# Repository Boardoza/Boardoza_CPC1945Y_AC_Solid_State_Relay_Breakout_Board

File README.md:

# Boardoza CPC1945Y Solid State Relay Breakout Board

The **Boardoza CPC1945Y Breakout Board** is built around the **CPC1945Y AC Solid State Relay (SSR)**, providing safe, silent, and reliable switching of low-power AC loads. Thanks to its optically isolated input and zero-crossing detection structure, it enables noise-free AC switching directly from microcontroller systems.

This board is ideal for applications such as **multiplexers, data acquisition systems, industrial control units, electronic meters (electricity, gas, water), medical devices, security systems, I/O subsystems**, and as a compact and long-lasting **solid-state replacement for mechanical relays**. With no mechanical contacts, it ensures long operational life and vibration-resistant performance.

## [Click here to purchase!](https://www.ozdisan.com/ureticiler/boardoza)

| Front Side | Back Side |
|:---:|:---:|
|  |  |

---

## Key Features

- **Solid State Relay:** Enables reliable AC switching with integrated zero-cross detection for clean transitions.  
- **Optical Isolation:** Provides safe electrical separation between low-voltage control circuits and high-voltage AC loads.  
- **Silent Operation:** No mechanical components, ensuring completely noise-free switching.  
- **Microcontroller Friendly:** Low input current requirement allows direct control from MCU GPIO pins.  
- **Low EMI/RFI:** Zero-cross switching significantly reduces electrical noise during operation.   

---

## Technical Specifications

**Model:** CPC1945Y  
**Manufacturer:** Boardoza  
**Manufacturer IC:** Littelfuse (IXYS Integrated Circuits Division)  
**Functions:** AC Solid State Relay (Optically Isolated)  
**Input Control Type:** DC (LED driven)  
**Typical Input Current:** 5 mA  
**Maximum Recommended Input Current:** 10 mA  
**Output Type:** AC (Zero-Cross)  
**Operating Load Voltage:** 20 – 120 Vac rms  
**Load Current:** Up to 1 A rms    
**Blocking Voltage:** 400 Vp  
**Isolation Voltage:** 3750 Vrms (Input to Output)  
**Operating Temperature:** -40°C to +85°C  
**Board Dimensions:** 20mm x 40mm  

---

## Board Pinout

### ( J1 ) Control Input Connector

| Pin Number | Pin Name | Description |
|:---:|:---:|---|
| 1 | CONTROL | DC Control Input (LED Anode) |
| 2 | GND | Ground (LED Cathode) |

---

### ( J2 ) AC Load Connector

| Pin Number | Pin Name | Description |
|:---:|:---:|---|
| 1 | AC LOAD | AC Output Terminal |
| 2 | AC LOAD | AC Output Terminal |

> The output terminals are non-polarized and internally connected to the SSR output stage.

---

## Board Dimensions

---

## Step Files

[Boardoza CPC1945Y.step](./assets/CPC1945Y%20Step.step)

---

## Datasheet

[CPC1945Y Datasheet.pdf](./assets/CPC1945Y%20Datasheet.pdf)

---

## Version History

- V1.0.0 - Initial Release  

---

## Support

- If you have any questions or need support, please contact **support@boardoza.com**

---

## **License**

### **Hardware Design**

[![CC BY-SA 4.0][cc-by-sa-shield]][cc-by-sa]

All hardware design files are licensed under [Creative Commons Attribution-ShareAlike 4.0 International License][cc-by-sa].

[cc-by-sa]: http://creativecommons.org/licenses/by-sa/4.0/
[cc-by-sa-shield]: https://img.shields.io/badge/License-CC%20BY--SA%204.0-lightgrey.svg

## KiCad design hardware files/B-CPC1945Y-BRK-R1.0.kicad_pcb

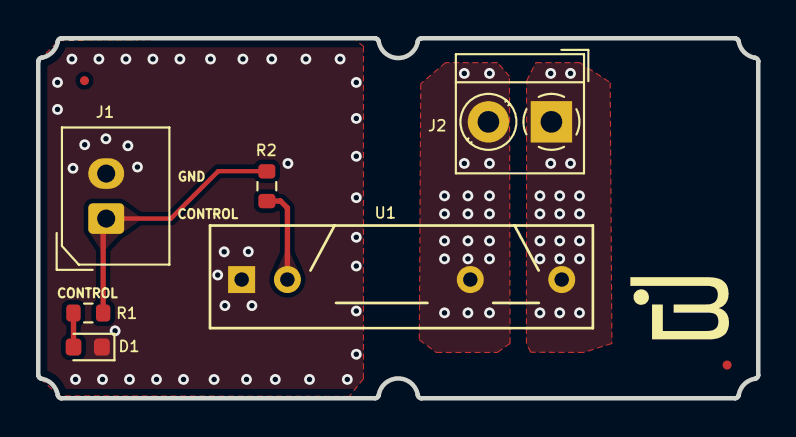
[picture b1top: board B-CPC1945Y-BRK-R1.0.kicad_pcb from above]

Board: 2 copper layers, 40.0 x 20.0 mm, 6 parts (0 on the bottom side), 6 nets.

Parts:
D1: LED; LED_0603_1608Metric
J1: Conn_01x02; 2317-02S_1x02_P2.50mm_Vertical
J2: Screw_Terminal_01x02; TerminalBlock_MetzConnect_Type059_RT06302HBWC_1x02_P3.50mm_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
R1: 470; R_0603_1608Metric
R2: 1k; R_0603_1608Metric
U1: CPC1945Y; SIP4_Sharp-SSR_P7.62mm_Straight

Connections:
/Control: J1.1, R1.2, R2.1
GND: D1.1 (K), J1.2, U1.1
unnamed: D1.2 (A), R1.1
unnamed: J2.1, U1.8
unnamed: J2.2, U1.6
unnamed: R2.2, U1.2
